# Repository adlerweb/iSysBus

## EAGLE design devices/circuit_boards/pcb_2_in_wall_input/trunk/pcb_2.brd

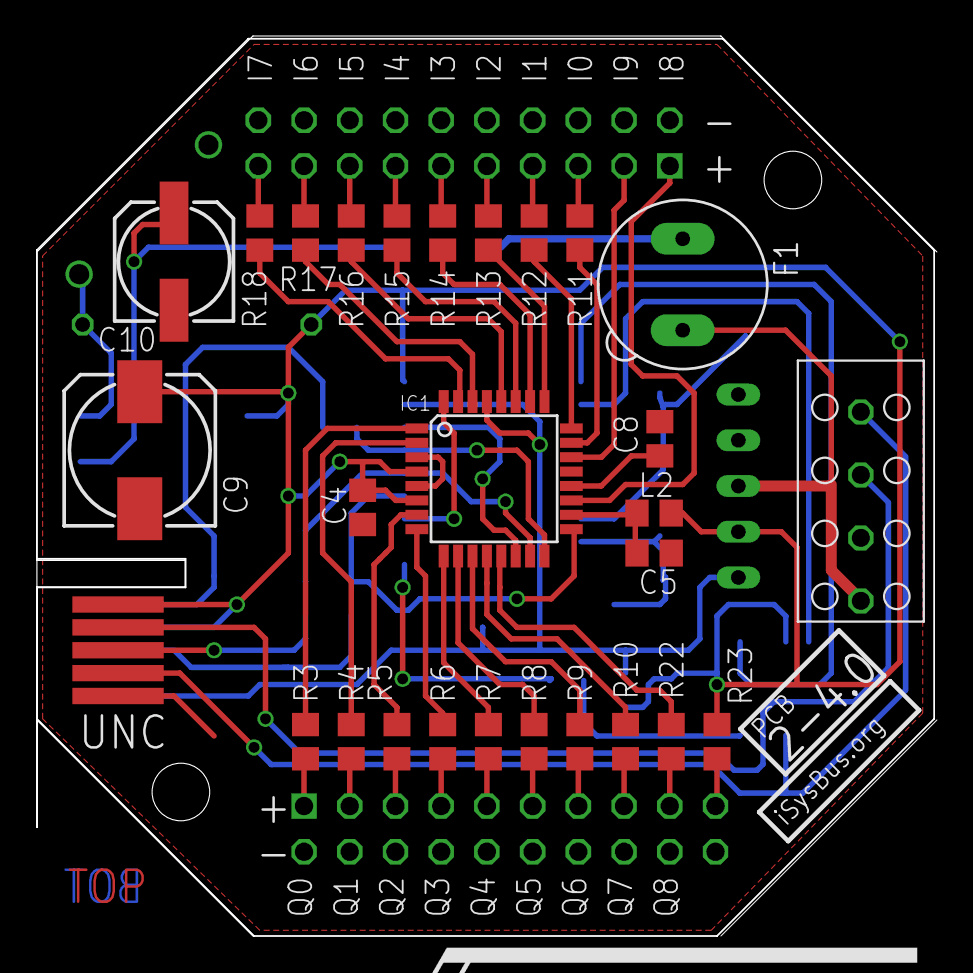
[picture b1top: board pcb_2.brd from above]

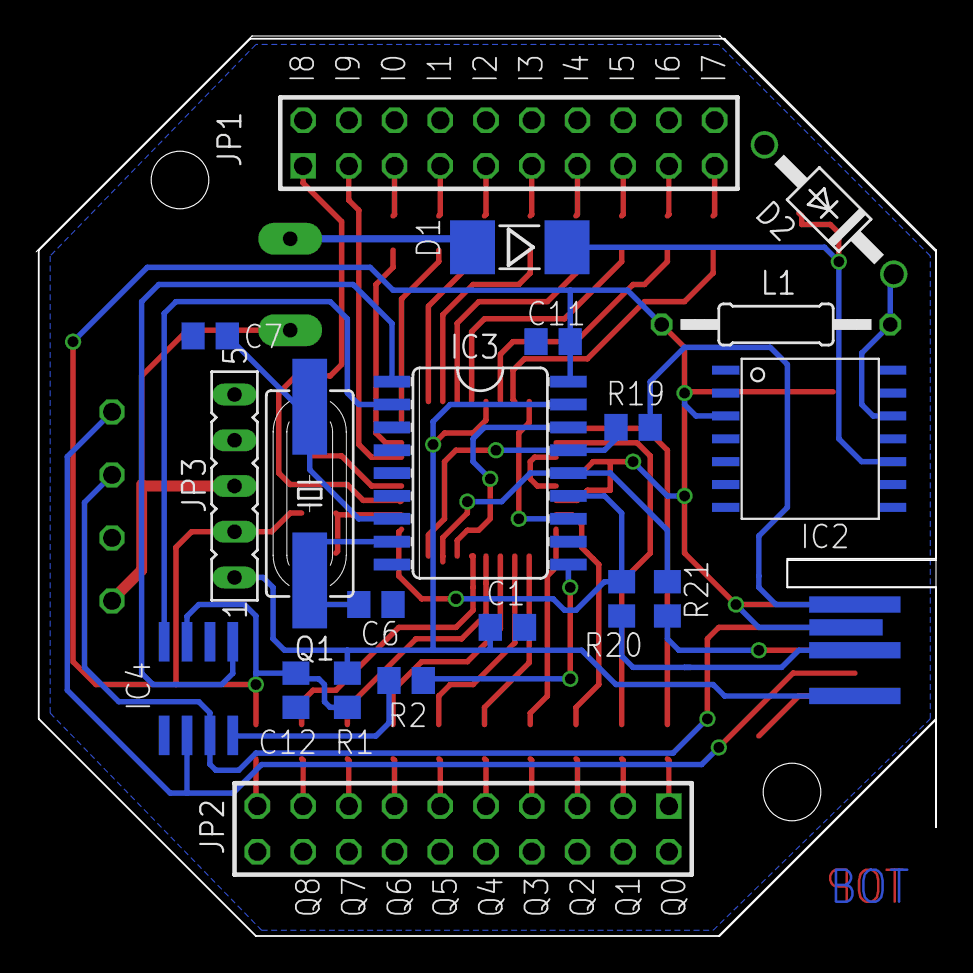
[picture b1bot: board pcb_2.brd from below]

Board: 2 copper layers, 50.0 x 50.0 mm, 54 parts (20 on the bottom side), 62 nets.

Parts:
C1, C4, C5, C8, C11, C12: 100n; C0805
C6, C7: 22p; C0805
C9: 330µ/16V; 153CLV-0810
C10: 22µ/35V; 153CLV-0605
D1: 1N4001SMD; MELF
D2: MUR110; DO41-10
F1: 315mA; 19560
IC1: ATMEGA168; TQFP32-08
IC2: LM257414WM; 14WM
IC3: MCP2515SO; SO18L
IC4: PCA82C250T; SO08
JP1: IN; 2X10
JP2: OUT; 2X10
JP3: SUP; FE05-1
L1: 470µ; 0207/12
L2: 10µ; L0805
Q1: 4M; HC49UP
R1: 10k; R0805
R2: 82k; R0805
R3, R4, R5, R6, R7, R8, R9, R10, R11, R12, R13, R14, R15, R16, R17, R18, R19, R20, R21, R22: 1k5; R0805
R23: 0R; R0805
U$1: ISYSBUS_LOGO
U$2: FIELD_ISB_PLACE
U$3: 2-4.0; FIELD_PCB_PLACE
UNC: UNC_ISP; UNC_PADS_ISP
UNC_CAN1: UNC_CAN; UNC_PADS_CAN
UNC_DP1: UNC_DP; UNC_PADS_DP
UNC_SUPPLY1: UNC_SUPPLY; UNC_PADS_SUPPLY
X1: iSysBus; PHOENIX_FK-MPT_4

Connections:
+24V: F1.2, JP3.3, X1.1
CAN_H: IC4.7, UNC_CAN1.B2, X1.3
CAN_L: IC4.6, UNC_CAN1.B4, X1.4
GND: C1.2, C4.2, C5.2, C6.2, C7.2, C8.2, C9.-, C10.-, C11.2, C12.2, D2.A, IC1.3, IC1.5, IC1.21, IC2.4, IC2.5, IC2.6, IC3.9, IC4.2, JP1.2, JP1.4, JP1.6, JP1.8, JP1.10, JP1.12, JP1.14, JP1.16, JP1.18, JP1.20, JP2.2, JP2.4, JP2.6, JP2.8, JP2.10, JP2.12, JP2.14, JP2.16, JP2.18, JP2.20, JP3.5, UNC_SUPPLY1.B5, X1.2
IN0: IC1.23, R11.1
IN1: IC1.24, R12.1
IN2: IC1.25, R13.1
IN3: IC1.26, R14.1
IN4: IC1.27, R15.1
IN5: IC1.28, R16.1
IN6: IC1.30, R17.1
IN7: IC1.31, R18.1
IN8: IC1.19, JP1.1
IN9: IC1.22, JP1.3
INT: IC1.32, IC3.12
MISO: IC1.16, IC3.15, R19.1
MOSI: IC1.15, IC3.14, R21.1
unnamed: D1.A, F1.1
unnamed: C5.1, IC1.18, L2.2
unnamed: D2.C, IC2.12, L1.2
unnamed: IC4.8, R2.2
unnamed: C6.1, IC3.8, Q1.1
unnamed: C8.1, IC1.20
unnamed: IC3.1, IC4.1
unnamed: IC3.2, IC4.4
unnamed: C7.1, IC3.7, Q1.2
unnamed: JP2.19, R23.2
unnamed: JP2.1, R3.2
unnamed: JP2.3, R4.2
unnamed: JP2.5, R5.2
unnamed: JP2.7, R6.2
unnamed: JP2.9, R7.2
unnamed: JP2.11, R8.2
unnamed: JP2.13, R9.2
unnamed: JP2.15, R10.2
unnamed: JP1.19, R18.2
unnamed: JP1.17, R17.2
unnamed: JP1.15, R16.2
unnamed: JP1.13, R15.2
unnamed: JP1.11, R14.2
unnamed: JP1.9, R13.2
unnamed: JP1.7, R12.2
unnamed: JP1.5, R11.2
unnamed: R20.2, UNC.A3
unnamed: R19.2, UNC.A1
unnamed: R21.2, UNC.B3
unnamed: JP2.17, R22.2
OUT0: IC1.1, R3.1
OUT1: IC1.2, R4.1
OUT2: IC1.7, R5.1
OUT3: IC1.8, R6.1
OUT4: IC1.9, R7.1
OUT5: IC1.10, R8.1
OUT6: IC1.11, R9.1
OUT7: IC1.12, R10.1
OUT8: IC1.13, R22.1
RESET: C1.1, IC1.29, IC3.17, JP3.1, R1.1, UNC.A5
RS: IC3.10, R2.1
SCK: IC1.17, IC3.13, R20.1
SS: IC1.14, IC3.16
V+: C10.+, D1.C, IC2.10
VCC: C4.1, C9.+, C11.1, C12.1, IC1.4, IC1.6, IC2.3, IC3.18, IC4.3, JP3.2, L1.1, L2.1, R1.2, R23.1, UNC_DP1.A2, UNC_SUPPLY1.B1

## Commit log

2018-11-25 Import
